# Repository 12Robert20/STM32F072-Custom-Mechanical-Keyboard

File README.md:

# STM32F072 Custom Mechanical Keyboard Controller

A custom hardware controller and switch matrix PCB designed in KiCad, powered by the STMicroelectronics STM32F072CBU6 microcontroller. Built for standard ANSI/ISO mechanical keyboard configurations with full N-Key Rollover (NKRO), native USB Type-C connectivity, and hardware-level ESD protection.

## 1. Project Overview

This project implements a self-contained mechanical keyboard controller and matrix layout. The architecture was developed to prioritize reliability, low Bill-of-Materials (BOM) complexity, and robust electrical protection without requiring external crystals or SPI flash memories.

### Key Specifications

* **Microcontroller:** STM32F072CBU6 (Arm Cortex-M0, 48 MHz, UFQFPN-48 package)
* **Switch Matrix:** 6 rows $\times$ 17 columns (up to 102 switch positions)
* **Anti-Ghosting:** Individual 0603 switching diodes per key (Full NKRO)
* **USB Interface:** 16-pin USB Type-C with dual $5.1\ \text{k}\Omega$ CC pulldowns (UFP / Device mode)
* **ESD Protection:** STMicroelectronics USBLC6-2SC6 low-capacitance TVS diode array on USB $D+$ and $D-$ lines
* **Power Regulation:** Diodes Inc. AP2112K-3.3 LDO (3.3V, 600 mA output, high PSRR) with ceramic decoupling
* **Programming & Debug:** 4-pin SWD interface (ST-Link compatible) plus hardware Reset and Boot0 pushbuttons
* **Status Indicators:** 3 onboard 1206 LEDs for Caps Lock, Num Lock, and Scroll Lock
* **Impedance Control:** Controlled $90\ \Omega$ differential impedance on USB 2.0 Full-Speed lines

## 2. Architecture & Design Rationale

During initial schematic capture and floorplanning, three controller platforms were evaluated:

| Microcontroller | USB Architecture | External Flash Required | External Oscillator Required | Design Verdict |
| :--- | :--- | :--- | :--- | :--- |
| **RP2040** | USB 2.0 FS | Yes (External QSPI NOR) | Yes (12 MHz Crystal) | Higher BOM count and routing density |
| **CH552** | USB 2.0 FS | No (Internal) | No (Internal RC) | Low flash/RAM headroom, limited GPIO drive |
| **STM32F072CBU6** | USB 2.0 FS (Native) | No (128 KB On-Chip) | No (Clock Recovery System) | **Selected:** Clean single-chip layout, native DFU, robust tooling |

The STM32F072 utilizes internal Clock Recovery System (CRS) hardware to synchronize its internal 48 MHz high-speed oscillator (HSI48) directly to USB Start-of-Frame (SOF) packets. This eliminates the need for an external quartz crystal or resonator, saving board real estate and reducing susceptibility to mechanical shock.

## 3. Hardware Subsystems

### 3.1. Matrix Architecture (6 x 17)

The board routes 6 row lines (`ROW_0` through `ROW_5`) and 17 column lines (`COLS_0` through `COLS_16`).

* Standard keyboard rows: Function row, Number row, QWERTY, Home row, Bottom row, and Space/Modifier row.
* Each switch footprint is paired with a surface-mount 0603 diode oriented from row to column to prevent back-feeding and ghosting during simultaneous multi-key presses.

### 3.2. Power Supply (VBUS to +3.3V)

* **Input:** $5\ \text{V}$ nominal supplied via USB VBUS.
* **Regulation:** AP2112K-3.3 SOT-23-5 low-dropout linear regulator capable of supplying up to $600\ \text{mA}$ with low quiescent current and drop-out voltage of $\sim 250\ \text{mV}$ at full load.
* **Decoupling:** $1\ \mu\text{F}$ input and output MLCC ceramic capacitors supplemented by local $100\ \text{nF}$ decoupling caps adjacent to all MCU $V_{DD}$ pins.

### 3.3. USB-C Entry and Protection

* **Connector:** 16-pin USB Type-C receptacle (USB 2.0 signal lines only).
* **Configuration Channel:** Two independent $5.1\ \text{k}\Omega$ ($1\%$) pulldown resistors tied to `CC1` and `CC2` to request $5\ \text{V}$ at up to $3\ \text{A}$ from standard Type-C and Type-C PD source devices.
* **Transient Voltage Suppression (TVS):** An STMicroelectronics `USBLC6-2SC6` array placed directly adjacent to the USB receptacle clamps electrostatic discharge events up to $15\ \text{kV}$ air / $8\ \text{kV}$ contact without degrading $12\ \text{Mbps}$ Full-Speed differential signal integrity ($C_{I/O} < 3.5\ \text{pF}$).

### 3.4. Status Indicators

* 3 GPIO-driven indicator channels (`CAPS_LED`, `NUM_LED`, `SCRL_LED`).
* Output lines feature dedicated $200\ \Omega$ series current-limiting resistors paired with 1206 package status LEDs.

## 4. PCB Layout and Differential Routing

The PCB is implemented on a standard 2-layer FR-4 substrate ($1.6\ \text{mm}$ thickness):

* **USB Differential Pair:** Calculated and routed for a $90\ \Omega \pm 10\%$ differential impedance target ($Z_{\text{diff}}$):
  * Trace width: $0.28\ \text{mm}$
  * Differential spacing: $0.20\ \text{mm}$
  * An unbroken ground plane on Layer 2 directly references the pair from the receptacle through the TVS diode up to MCU pins `PA11` ($D-$) and `PA12` ($D+$).
* **Ground Return Paths:** Top and bottom layers utilize copper fills tied together with regular via stitching to minimize loop area across switch matrix column returns.
* **Mechanical Tolerances:** Solder mask expansions and component keep-outs are verified against mechanical plate cuts and switch housing footprints.

## 5. Firmware Support

The hardware is compatible with several embedded keyboard firmware ecosystems:

1. **QMK Firmware:** Using the ChibiOS HAL for STM32F072 targets (`STM32F072xB`).
2. **ZMK Firmware:** Via custom Zephyr board definitions.
3. **Bare-metal STM32Cube / Custom C:** Direct USB HID implementation using standard ST USB Device Middleware.

### Programming & Flashing

* **Initial Flashing (SWD):** Connect an ST-Link V2/V3 programmer to header `J2`:
  * Pin 1: `+3.3V`
  * Pin 2: `SWDIO` (PA13)
  * Pin 3: `SWCLK` (PA14)
  * Pin 4: `GND`
* **USB DFU Bootloader:** Hold down the onboard `BOOT0` button and toggle `RESET` to enter the internal ST factory system memory bootloader directly over USB Type-C.

## 6. Fabrication & Assembly Notes

* **Layer Count:** 2 layers
* **Minimum Trace / Space:** 0.2 mm / 0.2 mm
* **Minimum Via Size:** 0.3 mm drill / 0.6 mm annular ring
* **Surface Finish:** ENIG recommended (or Lead-free HASL)
* **Passive Packages:** 0603 (diode array and decoupling) / 1206 (indicator LEDs)
* **SMD IC Footprint:** UFQFPN-48 with central exposed thermal ground pad

## 7. Author & Inquiries

Designed by an independent hardware engineer specializing in KiCad PCB layout, embedded hardware design, and DFM optimization.

Open for freelance inquiries regarding schematic capture, board redesigns, and layout for prototype or production hardware. Direct messages can be sent via LinkedIn or GitHub issues.

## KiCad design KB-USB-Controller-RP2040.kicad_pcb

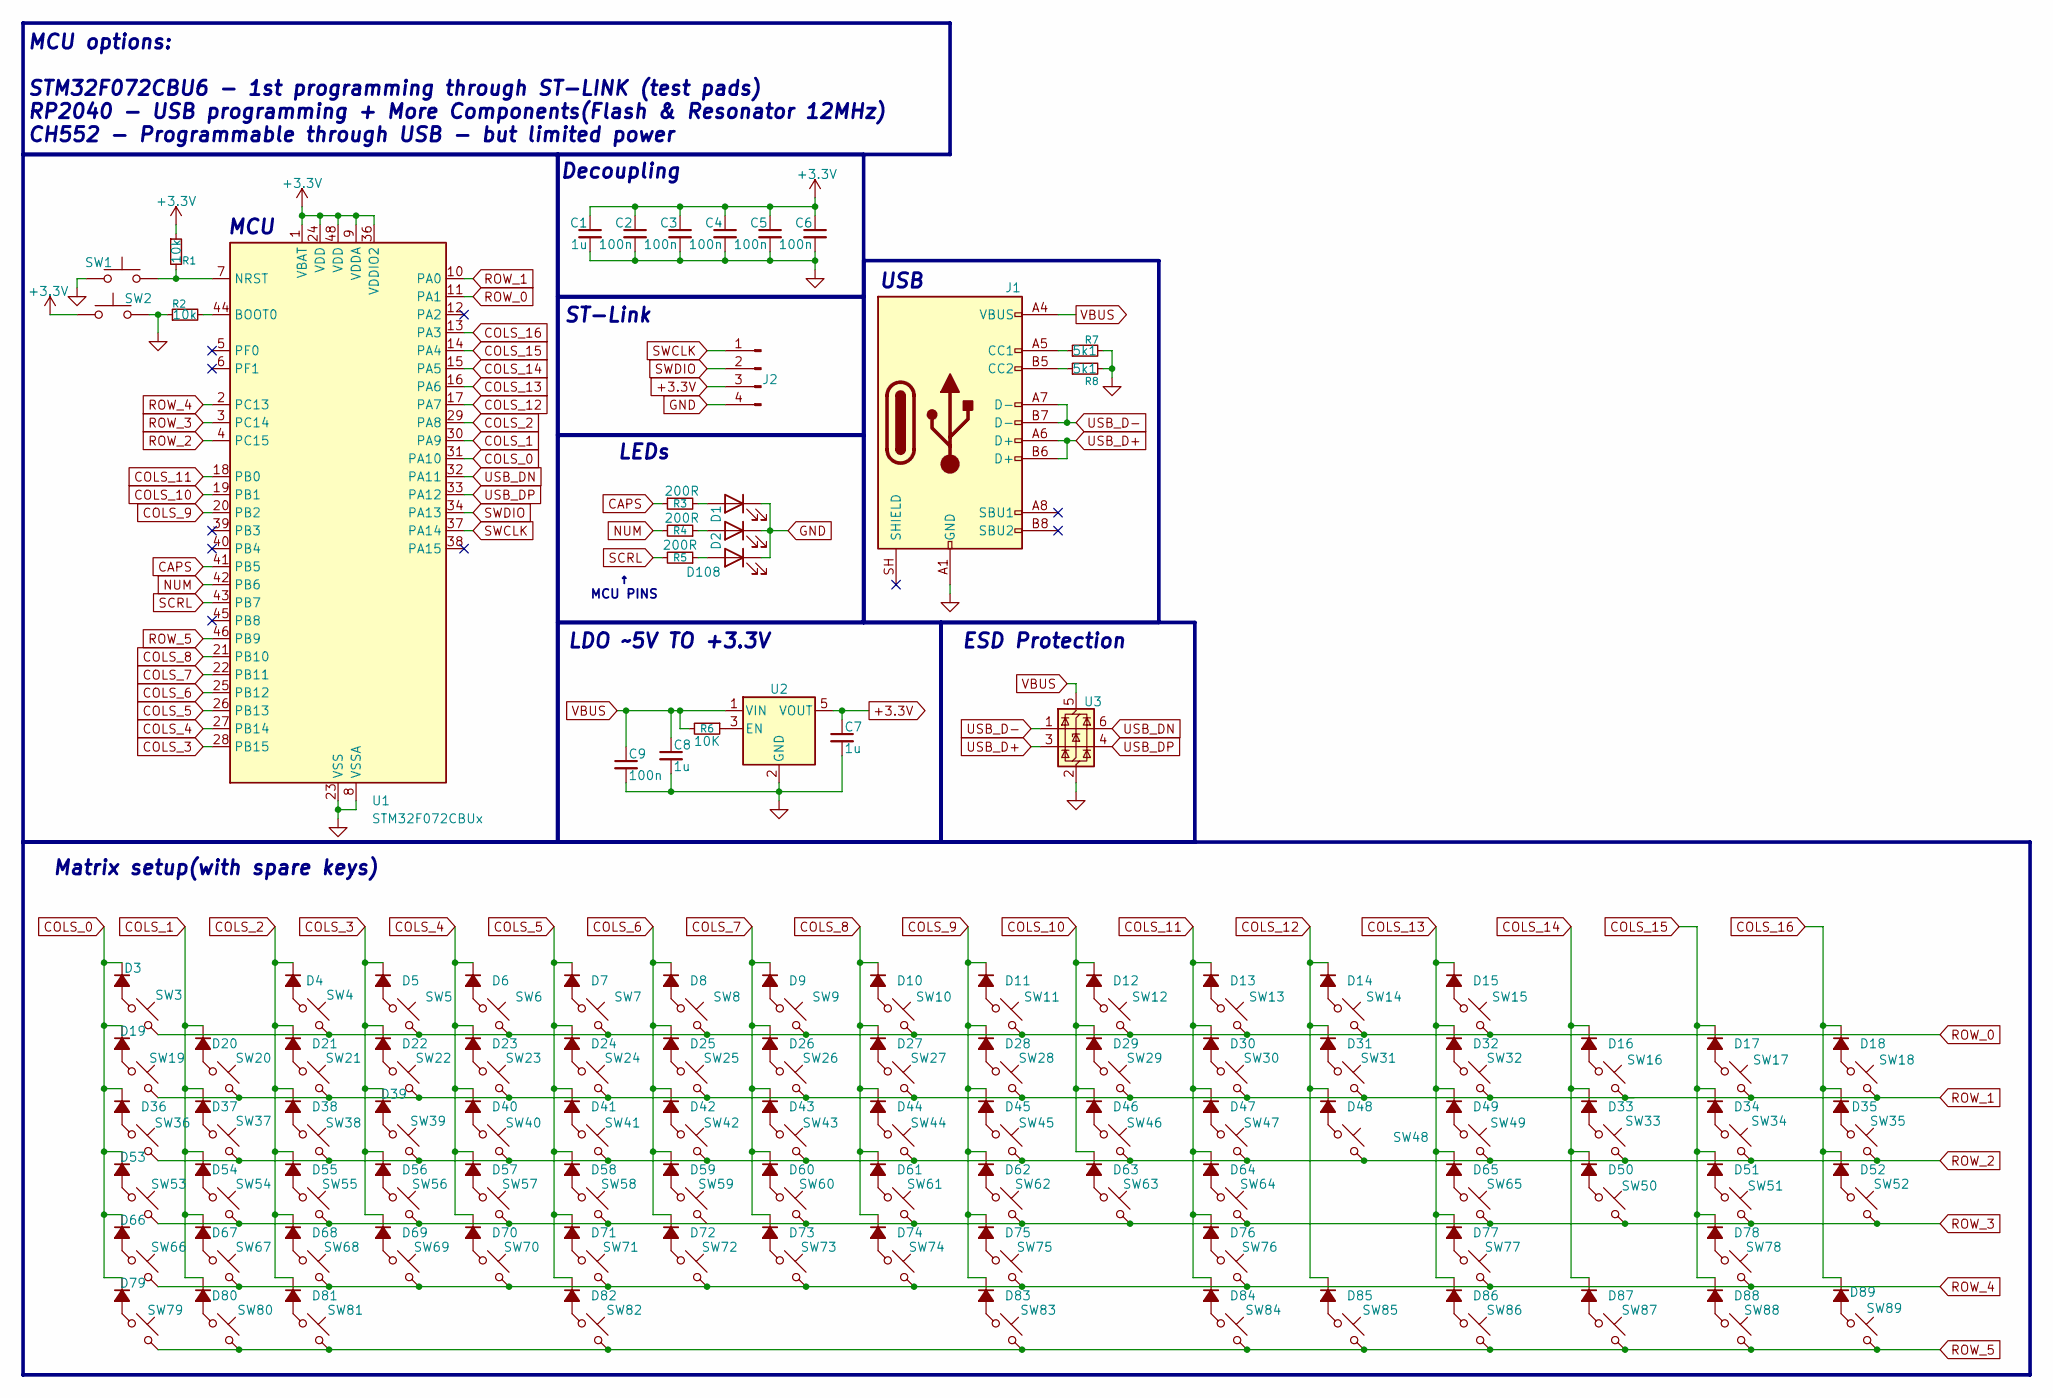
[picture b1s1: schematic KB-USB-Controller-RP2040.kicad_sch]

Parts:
C1, C7, C8: 1u; C_0805_2012Metric_Pad1.18x1.45mm_HandSolder
C2, C3, C4, C5, C6, C9: 100n; C_0603_1608Metric_Pad1.08x0.95mm_HandSolder
D1, D2, D108: LED; LED_1206_3216Metric_Pad1.42x1.75mm_HandSolder
D3, D4, D5, D6, D7, D8, D9, D10, D11, D12, D13, D14, D15, D16, D17, D18, D19, D20, D21, D22, D23, D24, D25, D26, D27, D28, D29, D30, D31, D32, D33, D34, D35, D36, D37, D38, D39, D40, D41, D42, D43, D44, D45, D46, D47, D48, D49, D50, D51, D52, D53, D54, D55, D56, D57, D58, D59, D60, D61, D62, D63, D64, D65, D66, D67, D68, D69, D70, D71, D72, D73, D74, D75, D76, D77, D78, D79, D80, D81, D82, D83, D84, D85, D86, D87, D88, D89: D_Small_Filled; D_0603_1608Metric_Pad1.05x0.95mm_HandSolder
J1: USB_C_Receptacle_USB2.0_16P; USB_C_Receptacle_GCT_USB4105-xx-A_16P_TopMnt_Horizontal
J2: Conn_01x04_Pin; SolderingWirePad_1x04_SMD_2x4mm
R1, R2: 10k; R_0603_1608Metric_Pad0.98x0.95mm_HandSolder
R3, R4, R5: 200R; R_0603_1608Metric_Pad0.98x0.95mm_HandSolder
R6: 10K; R_0603_1608Metric_Pad0.98x0.95mm_HandSolder
R7, R8: 5k1; R_0603_1608Metric_Pad0.98x0.95mm_HandSolder
SW1, SW2: SW_MEC_5G; SW_MEC_5GSH9
SW3, SW4, SW5, SW6, SW7, SW8, SW9, SW10, SW11, SW12, SW13, SW14, SW15, SW16, SW17, SW18, SW19, SW20, SW21, SW22, SW23, SW24, SW25, SW26, SW27, SW28, SW29, SW30, SW31, SW32, SW33, SW34, SW35, SW36, SW37, SW38, SW39, SW40, SW41, SW42, SW43, SW44, SW45, SW46, SW47, SW48, SW49, SW50, SW51, SW52, SW53, SW54, SW55, SW56, SW57, SW58, SW59, SW60, SW61, SW62, SW63, SW64, SW65, SW66, SW67, SW68, SW69, SW70, SW71, SW72, SW73, SW74, SW75, SW76, SW77, SW78, SW79, SW80, SW81, SW82, SW83, SW84, SW85, SW86, SW87, SW88, SW89: SW_Push_45deg; SW_Cherry_MX_1.50u_Plate
U1: STM32F072CBUx; QFN-48-1EP_7x7mm_P0.5mm_EP5.6x5.6mm
U2: AP2112K-3.3; SOT-23-5
U3: USBLC6-2SC6; SOT-23-6

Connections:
+3.3V: C1.1, C2.1, C3.1, C4.1, C5.1, C6.1, C7.1, J2.3, R1.1, SW2.1 (A), SW2.2 (A), U1.1 (VBAT), U1.9 (VDDA), U1.24 (VDD), U1.36 (VDDIO2), U1.48 (VDD), U2.5 (VOUT)
CAPS: R3.1, U1.41 (PB5)
COLS_0: D3.1 (K), D19.1 (K), D36.1 (K), D53.1 (K), D66.1 (K), D79.1 (K), U1.31 (PA10)
COLS_1: D20.1 (K), D37.1 (K), D54.1 (K), D67.1 (K), D80.1 (K), U1.30 (PA9)
COLS_2: D4.1 (K), D21.1 (K), D38.1 (K), D55.1 (K), D68.1 (K), D81.1 (K), U1.29 (PA8)
COLS_3: D5.1 (K), D22.1 (K), D39.1 (K), D56.1 (K), D69.1 (K), U1.28 (PB15)
COLS_4: D6.1 (K), D23.1 (K), D40.1 (K), D57.1 (K), D70.1 (K), U1.27 (PB14)
COLS_5: D7.1 (K), D24.1 (K), D41.1 (K), D58.1 (K), D71.1 (K), D82.1 (K), U1.26 (PB13)
COLS_6: D8.1 (K), D25.1 (K), D42.1 (K), D59.1 (K), D72.1 (K), U1.25 (PB12)
COLS_7: D9.1 (K), D26.1 (K), D43.1 (K), D60.1 (K), D73.1 (K), U1.22 (PB11)
COLS_8: D10.1 (K), D27.1 (K), D44.1 (K), D61.1 (K), D74.1 (K), U1.21 (PB10)
COLS_9: D11.1 (K), D28.1 (K), D45.1 (K), D62.1 (K), D75.1 (K), D83.1 (K), U1.20 (PB2)
COLS_10: D12.1 (K), D29.1 (K), D46.1 (K), D63.1 (K), U1.19 (PB1)
COLS_11: D13.1 (K), D30.1 (K), D47.1 (K), D64.1 (K), D76.1 (K), D84.1 (K), U1.18 (PB0)
COLS_12: D14.1 (K), D31.1 (K), D48.1 (K), D85.1 (K), U1.17 (PA7)
COLS_13: D15.1 (K), D32.1 (K), D49.1 (K), D65.1 (K), D77.1 (K), D86.1 (K), U1.16 (PA6)
COLS_14: D16.1 (K), D33.1 (K), D50.1 (K), D87.1 (K), U1.15 (PA5)
COLS_15: D17.1 (K), D34.1 (K), D51.1 (K), D78.1 (K), D88.1 (K), U1.14 (PA4)
COLS_16: D18.1 (K), D35.1 (K), D52.1 (K), D89.1 (K), U1.13 (PA3)
GND: C1.2, C2.2, C3.2, C4.2, C5.2, C6.2, C7.2, C8.2, C9.2, D1.1 (K), D2.1 (K), D108.1 (K), J1.A1 (GND), J1.A12 (GND), J1.B1 (GND), J1.B12 (GND), J2.4, R2.1, R7.2, R8.2, SW1.1 (A), SW1.2 (A), SW2.3 (B), SW2.4 (B), U1.8 (VSSA), U1.23 (VSS), U1.35 (VSS), U1.47 (VSS), U1.49 (VSS), U2.2 (GND), U3.2 (GND)
NUM: R4.2, U1.42 (PB6)
unnamed: D1.2 (A), R3.2
unnamed: D2.2 (A), R4.1
unnamed: D3.2 (A), SW3.1
unnamed: D4.2 (A), SW4.1
unnamed: D5.2 (A), SW5.1
unnamed: D6.2 (A), SW6.1
unnamed: D7.2 (A), SW7.1
unnamed: D8.2 (A), SW8.1
unnamed: D9.2 (A), SW9.1
unnamed: D10.2 (A), SW10.1
unnamed: D11.2 (A), SW11.1
unnamed: D12.2 (A), SW12.1
unnamed: D13.2 (A), SW13.1
unnamed: D14.2 (A), SW14.1
unnamed: D15.2 (A), SW15.1
unnamed: D16.2 (A), SW16.1
unnamed: D17.2 (A), SW17.1
unnamed: D18.2 (A), SW18.1
unnamed: D19.2 (A), SW19.1
unnamed: D20.2 (A), SW20.1
unnamed: D21.2 (A), SW21.1
unnamed: D22.2 (A), SW22.1
unnamed: D23.2 (A), SW23.1
unnamed: D24.2 (A), SW24.1
unnamed: D25.2 (A), SW25.1
unnamed: D26.2 (A), SW26.1
unnamed: D27.2 (A), SW27.1
unnamed: D28.2 (A), SW28.1
unnamed: D29.2 (A), SW29.1
unnamed: D30.2 (A), SW30.1
unnamed: D31.2 (A), SW31.1
unnamed: D32.2 (A), SW32.1
unnamed: D33.2 (A), SW33.1
unnamed: D34.2 (A), SW34.1
unnamed: D35.2 (A), SW35.1
unnamed: D36.2 (A), SW36.1
unnamed: D37.2 (A), SW37.1
unnamed: D38.2 (A), SW38.1
unnamed: D39.2 (A), SW39.1
unnamed: D40.2 (A), SW40.1
unnamed: D41.2 (A), SW41.1
unnamed: D42.2 (A), SW42.1
unnamed: D43.2 (A), SW43.1
unnamed: D44.2 (A), SW44.1
unnamed: D45.2 (A), SW45.1
unnamed: D46.2 (A), SW46.1
unnamed: D47.2 (A), SW47.1
unnamed: D48.2 (A), SW48.1
unnamed: D49.2 (A), SW49.1
unnamed: D50.2 (A), SW50.1
unnamed: D51.2 (A), SW51.1
unnamed: D52.2 (A), SW52.1
unnamed: D53.2 (A), SW53.1
unnamed: D54.2 (A), SW54.1
unnamed: D55.2 (A), SW55.1
unnamed: D56.2 (A), SW56.1
unnamed: D57.2 (A), SW57.1
unnamed: D58.2 (A), SW58.1
unnamed: D59.2 (A), SW59.1 (1_1)
unnamed: D60.2 (A), SW60.1
unnamed: D61.2 (A), SW61.1
unnamed: D62.2 (A), SW62.1
unnamed: D63.2 (A), SW63.1
unnamed: D64.2 (A), SW64.1
unnamed: D65.2 (A), SW65.1
unnamed: D66.2 (A), SW66.1
unnamed: D67.2 (A), SW67.1
unnamed: D68.2 (A), SW68.1
unnamed: D69.2 (A), SW69.1
unnamed: D70.2 (A), SW70.1
unnamed: D71.2 (A), SW71.1
unnamed: D72.2 (A), SW72.1
unnamed: D73.2 (A), SW73.1
unnamed: D74.2 (A), SW74.1
unnamed: D75.2 (A), SW75.1
unnamed: D76.2 (A), SW76.1
unnamed: D77.2 (A), SW77.1
unnamed: D78.2 (A), SW78.1
unnamed: D79.2 (A), SW79.1
unnamed: D80.2 (A), SW80.1
unnamed: D81.2 (A), SW81.1
unnamed: D82.2 (A), SW82.1
unnamed: D83.2 (A), SW83.1
unnamed: D84.2 (A), SW84.1
unnamed: D85.2 (A), SW85.1
unnamed: D86.2 (A), SW86.1
unnamed: D87.2 (A), SW87.1
unnamed: D88.2 (A), SW88.1
unnamed: D89.2 (A), SW89.1
unnamed: D108.2 (A), R5.1
unnamed: J1.A5 (CC1), R7.1
unnamed: J1.B5 (CC2), R8.1
unnamed: R2.2, U1.44 (BOOT0)
unnamed: R1.2, SW1.3 (B), SW1.4 (B), U1.7 (NRST)
unnamed: R6.1, U2.3 (EN)
ROW_0: SW3.2, SW4.2, SW5.2, SW6.2, SW7.2, SW8.2, SW9.2, SW10.2, SW11.2, SW12.2, SW13.2, SW14.2, SW15.2, U1.11 (PA1)
ROW_1: SW16.2, SW17.2, SW18.2, SW19.2, SW20.2, SW21.2, SW22.2, SW23.2, SW24.2, SW25.2, SW26.2, SW27.2, SW28.2, SW29.2, SW30.2, SW31.2, SW32.2, U1.10 (PA0)
ROW_2: SW33.2, SW34.2, SW35.2, SW36.2, SW37.2, SW38.2, SW39.2, SW40.2, SW41.2, SW42.2, SW43.2, SW44.2, SW45.2, SW46.2, SW47.2, SW48.2, SW49.2, U1.4 (PC15)
ROW_3: SW50.2, SW51.2, SW52.2, SW53.2, SW54.2, SW55.2, SW56.2, SW57.2, SW58.2, SW60.2, SW61.2, SW62.2, SW63.2, SW64.2, SW65.2, U1.3 (PC14)
ROW_4: SW66.2, SW67.2, SW68.2, SW69.2, SW70.2, SW71.2, SW72.2, SW73.2, SW74.2, SW75.2, SW76.2, SW77.2, SW78.2, U1.2 (PC13)
ROW_5: SW79.2, SW80.2, SW81.2, SW82.2, SW83.2, SW84.2, SW85.2, SW86.2, SW87.2, SW88.2, SW89.2, U1.46 (PB9)
SCRL: R5.2, U1.43 (PB7)
SWCLK: J2.1, U1.37 (PA14)
SWDIO: J2.2, U1.34 (PA13)
USB_D+: J1.A6 (D+), J1.B6 (D+), U3.3 (I/O2)
USB_D-: J1.A7 (D-), J1.B7 (D-), U3.1 (I/O1)
USB_DN: U1.32 (PA11), U3.6 (I/O1)
USB_DP: U1.33 (PA12), U3.4 (I/O2)
VBUS: C8.1, C9.1, J1.A4 (VBUS), J1.A9 (VBUS), J1.B4 (VBUS), J1.B9 (VBUS), R6.2, U2.1 (VIN), U3.5 (VBUS)

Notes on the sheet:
ESD Protection
ST-Link
Matrix setup(with spare keys)
LEDs
MCU
LDO ~5V TO +3.3V
Decoupling
MCU options: STM32F072CBU6 - 1st programming through ST-LINK (test pads) RP2040 - USB programming + More Components(Flash & Resonator 12MHz) CH552 - Programmable through USB - but limited power
↑ MCU PINS
USB

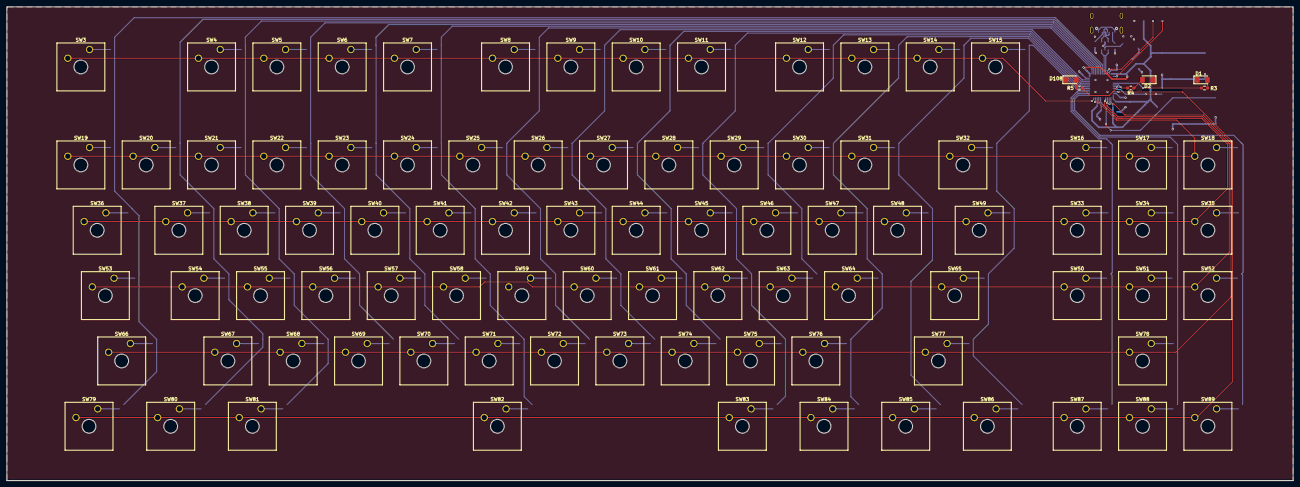
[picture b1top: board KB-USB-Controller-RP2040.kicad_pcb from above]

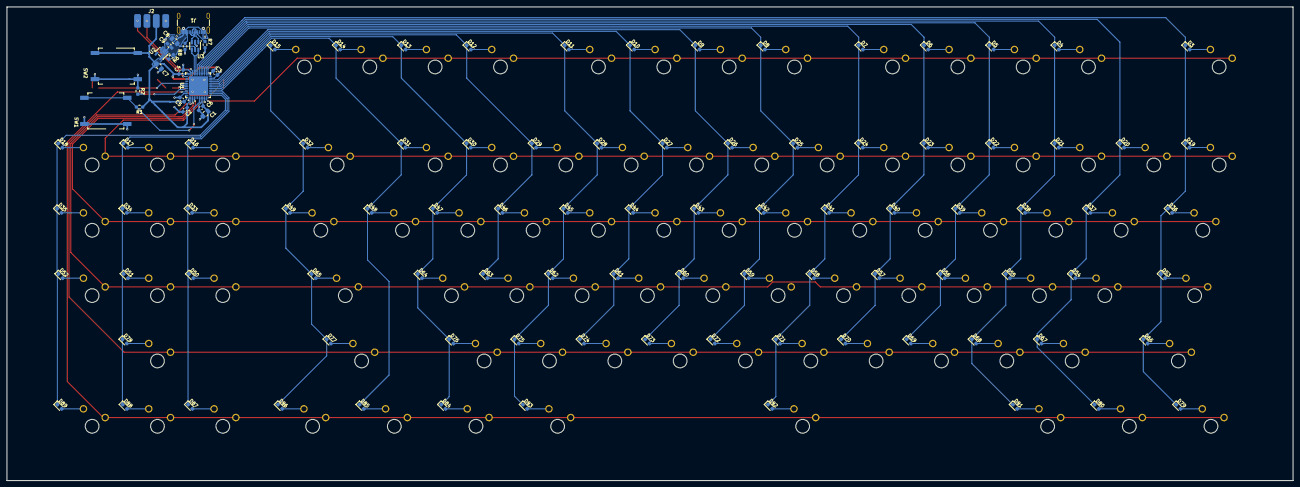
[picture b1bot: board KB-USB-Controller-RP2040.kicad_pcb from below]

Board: 2 copper layers, 375.0 x 138.1 mm, 201 parts (108 on the bottom side), 130 nets.
